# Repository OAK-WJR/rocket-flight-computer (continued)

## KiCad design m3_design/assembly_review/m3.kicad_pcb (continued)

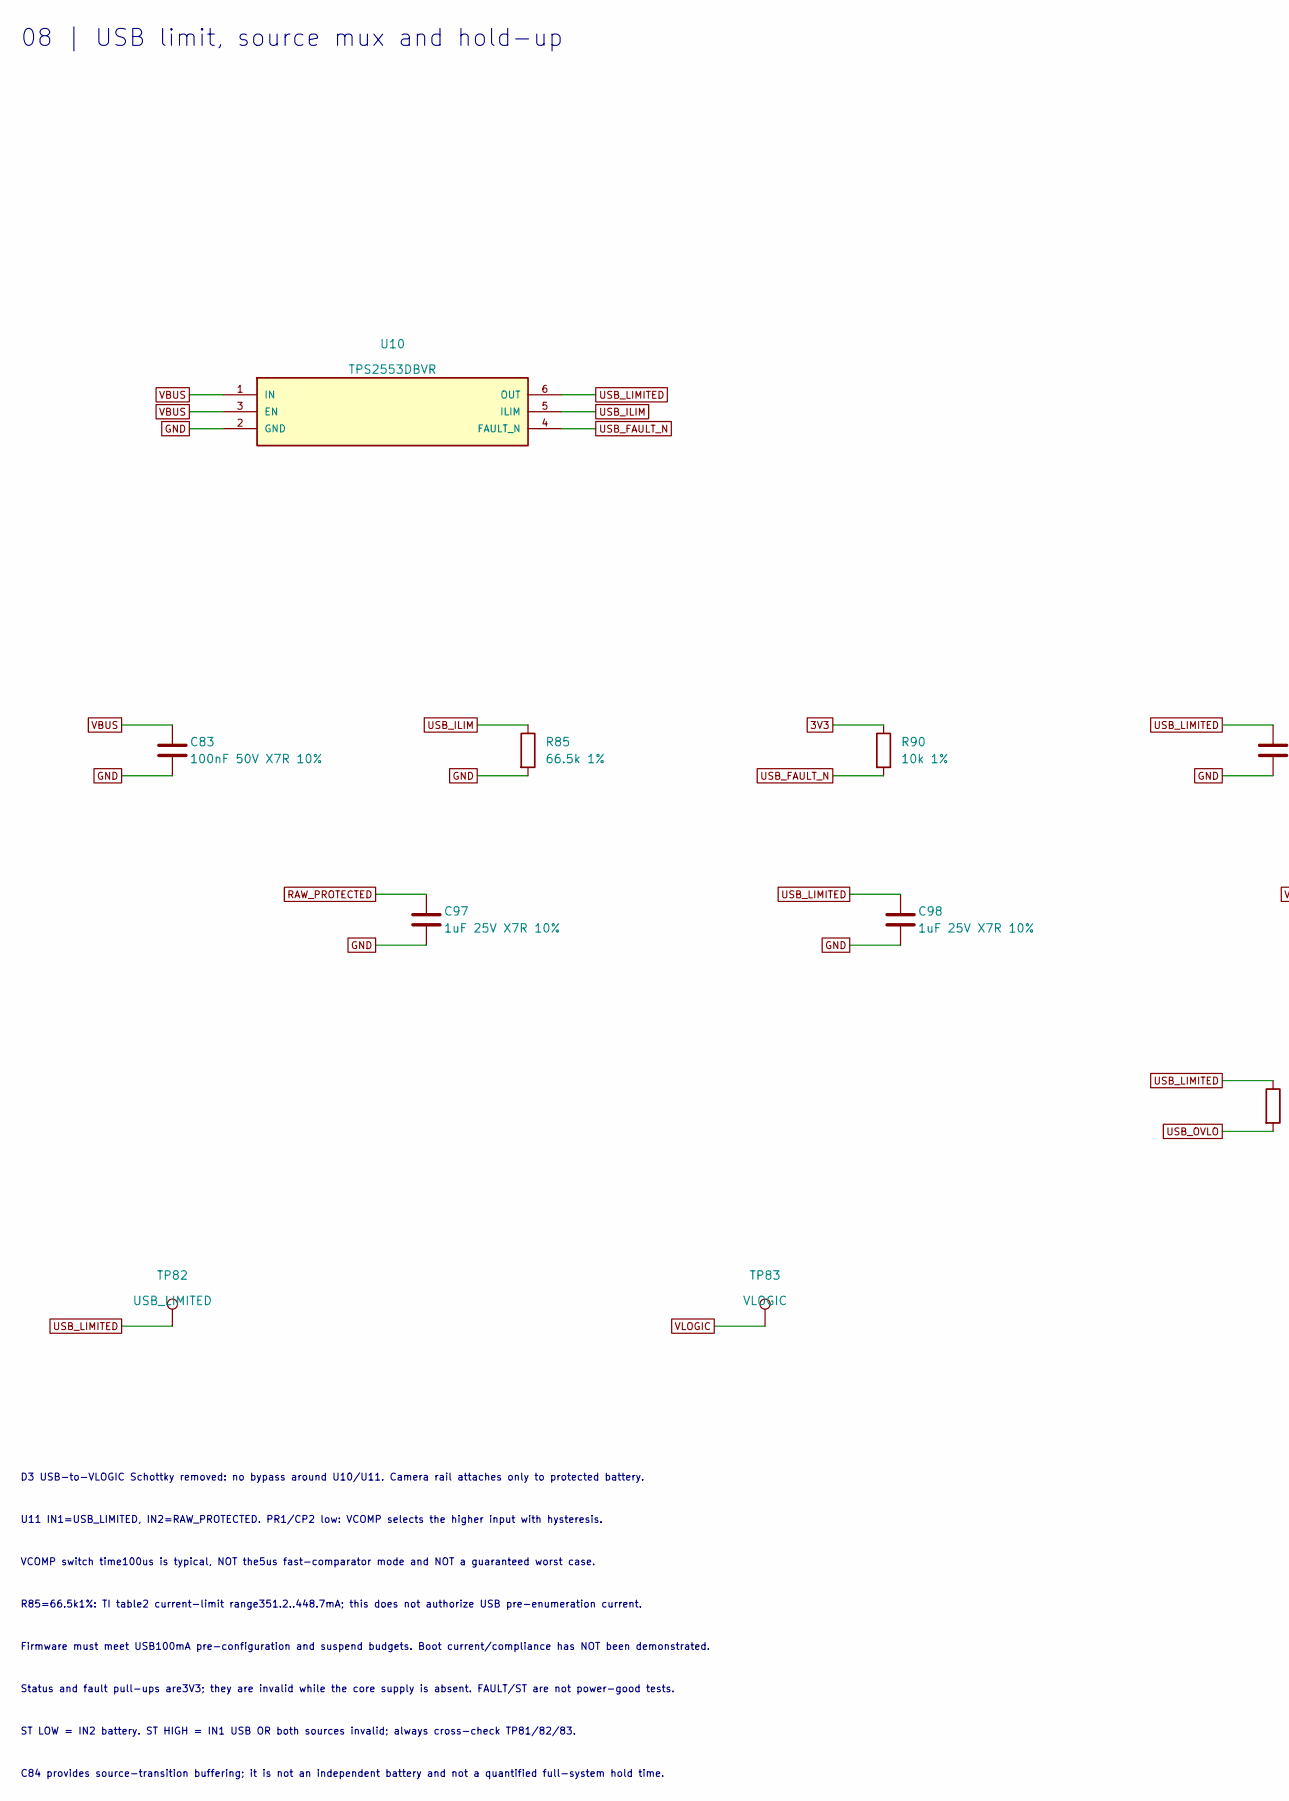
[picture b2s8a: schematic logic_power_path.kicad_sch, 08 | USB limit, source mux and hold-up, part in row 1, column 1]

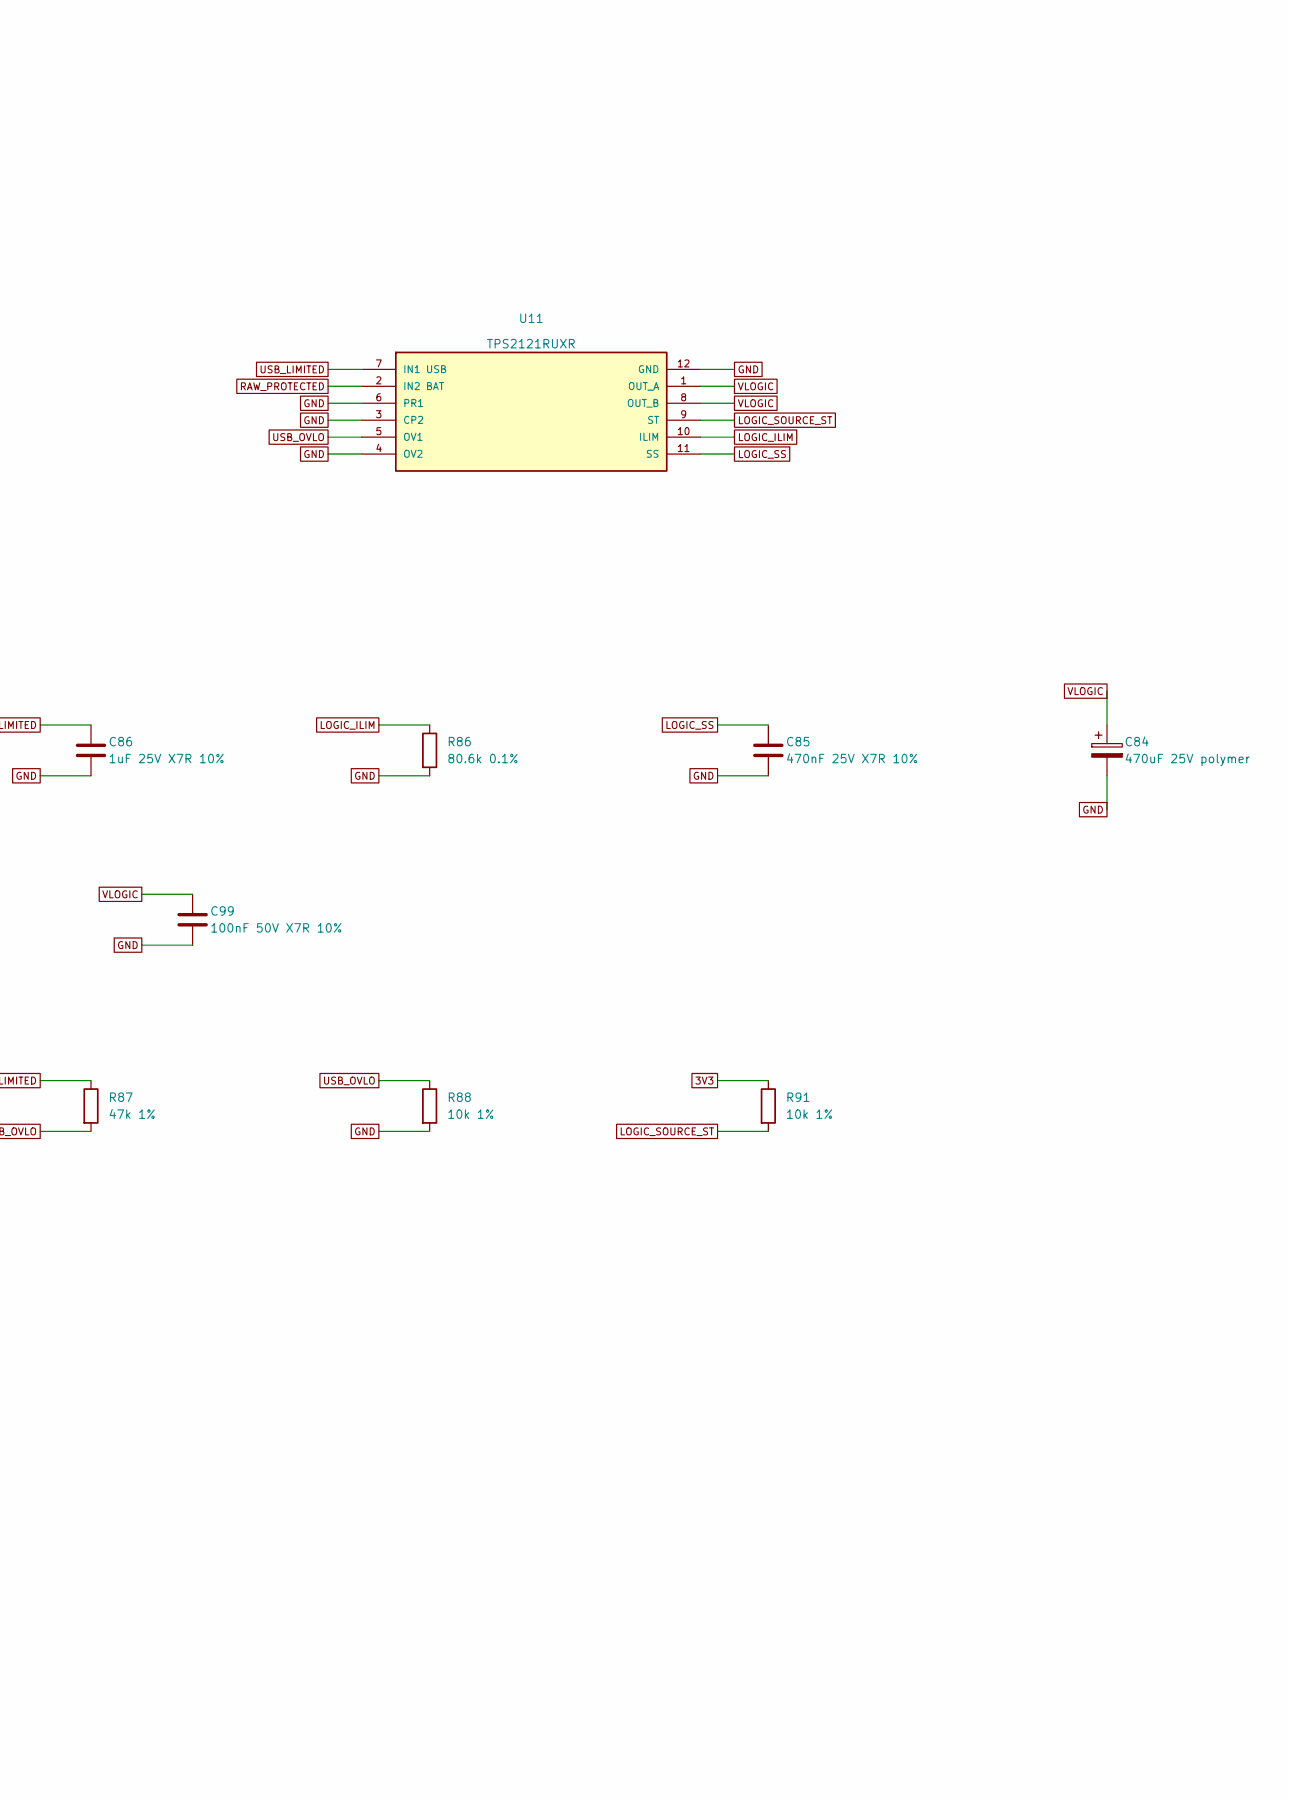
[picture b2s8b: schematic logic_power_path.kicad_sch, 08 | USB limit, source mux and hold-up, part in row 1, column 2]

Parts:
C83: 100nF 50V X7R 10%; C_0603_1608Metric; Manufacturer Part CC0603KRX7R9BB104; LCSC C14663
C84: 470uF 25V polymer; M3_MA_8x10; Manufacturer Part MA25V470M8x10; LCSC C46550466
C85: 470nF 25V X7R 10%; C_0603_1608Metric; Manufacturer Part CL10B474KA8NNNC; LCSC C1623
C86, C97, C98: 1uF 25V X7R 10%; C_0603_1608Metric; Manufacturer Part CL10B105KA8NNNC; LCSC C29936
C99: 100nF 50V X7R 10%; C0402; Manufacturer Part CL05B104KB54PNC; LCSC C307331
R85: 66.5k 1%; R_0603_1608Metric; Manufacturer Part RC0603FR-0766K5L; LCSC C137691
R86: 80.6k 0.1%; R_0603_1608Metric; Manufacturer Part RT0603BRD0780K6L; LCSC C861568
R87: 47k 1%; R_0603_1608Metric; Manufacturer Part 0603WAF4702T5E; LCSC C25819
R88, R90, R91: 10k 1%; R_0603_1608Metric; Manufacturer Part 0603WAF1002T5E; LCSC C25804
TP82: USB_LIMITED; M3_TestPad_1.5
TP83: VLOGIC; M3_TestPad_1.5
U10: TPS2553DBVR; M3_TPS2553_DBV; Manufacturer Part TPS2553DBVR; LCSC C55266
U11: TPS2121RUXR; M3_TPS2121_RUX; Manufacturer Part TPS2121RUXR; LCSC C485916

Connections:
3V3: R90.1, R91.1; also elsewhere on the board
GND: C83.2, C84.2, C85.2, C86.2, C97.2, C98.2, C99.2, R85.2, R86.2, R88.2, U10.2 (GND), U11.3 (CP2), U11.4 (OV2), U11.6 (PR1), U11.12 (GND); also elsewhere on the board
LOGIC_ILIM: R86.1, U11.10 (ILIM)
LOGIC_SOURCE_ST: R91.2, U11.9 (ST); also elsewhere on the board
LOGIC_SS: C85.1, U11.11 (SS)
RAW_PROTECTED: C97.1, U11.2 (IN2 BAT); also elsewhere on the board
USB_FAULT_N: R90.2, U10.4 (FAULT_N); also elsewhere on the board
USB_ILIM: R85.1, U10.5 (ILIM)
USB_LIMITED: C86.1, C98.1, R87.1, TP82.1, U10.6 (OUT), U11.7 (IN1 USB)
USB_OVLO: R87.2, R88.1, U11.5 (OV1)
VBUS: C83.1, U10.1 (IN), U10.3 (EN); also elsewhere on the board
VLOGIC: C84.1, C99.1, TP83.1, U11.1 (OUT_A), U11.8 (OUT_B); also elsewhere on the board

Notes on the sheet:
08 | USB limit, source mux and hold-up
D3 USB-to-VLOGIC Schottky removed: no bypass around U10/U11. Camera rail attaches only to protected battery.
U11 IN1=USB_LIMITED, IN2=RAW_PROTECTED. PR1/CP2 low: VCOMP selects the higher input with hysteresis.
VCOMP switch time100us is typical, NOT the5us fast-comparator mode and NOT a guaranteed worst case.
R85=66.5k1%: TI table2 current-limit range351.2..448.7mA; this does not authorize USB pre-enumeration current.
Firmware must meet USB100mA pre-configuration and suspend budgets. Boot current/compliance has NOT been demonstrated.
Status and fault pull-ups are3V3; they are invalid while the core supply is absent. FAULT/ST are not power-good tests.
ST LOW = IN2 battery. ST HIGH = IN1 USB OR both sources invalid; always cross-check TP81/82/83.
C84 provides source-transition buffering; it is not an independent battery and not a quantified full-system hold time.

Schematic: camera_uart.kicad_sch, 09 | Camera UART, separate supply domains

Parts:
C90, C93: 100nF 50V X7R 10%; C_0603_1608Metric; Manufacturer Part CC0603KRX7R9BB104; LCSC C14663
C91: 1uF 50V X7R 10%; C_1206_3216Metric; Manufacturer Part CL31B105KBHNNNE; LCSC C1848
C92: 4.7uF 16V X5R 10%; C0603; Manufacturer Part CL10A475KO8NNNC; LCSC C19666
C100: 100nF 50V X7R 10%; C0402; Manufacturer Part CL05B104KB54PNC; LCSC C307331
D400, D401: ESD103-B1-02EL; M3_TSLP_2_20; Manufacturer Part ESD103-B1-02EL E6327; LCSC C535146
R100, R101, R103: 1k 1%; R_0603_1608Metric; Manufacturer Part 0603WAF1001T5E; LCSC C21190
R102: 10k 1%; R_0603_1608Metric; Manufacturer Part 0603WAF1002T5E; LCSC C25804
U12: TXU0202DCUR; M3_TXU0202_DCU; Manufacturer Part TXU0202DCUR; LCSC C5186957
U13: TPS70933DBVR; M3_TPS709_DBV; Manufacturer Part TPS70933DBVR; LCSC C89347

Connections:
3V3: C90.1, C100.1, U12.3 (VCCA MCU); also elsewhere on the board
CAM_5V: C91.1, U13.1 (IN); also elsewhere on the board
CAM_IO_3V3: C92.1, C93.1, R103.1, U12.7 (VCCB CAMERA), U13.5 (OUT3.3V)
CAM_MCU_RX: U12.4 (A2Y RX OUTPUT); also elsewhere on the board
CAM_MCU_TX: U12.5 (A1 TX INPUT); also elsewhere on the board
CAM_RX_BUFFER: R100.2, U12.1 (B2 FROM CAMERA)
CAM_RX_WIRE: D401.1 (A1), R100.1; also elsewhere on the board
CAM_TX_BUFFER: R101.1, U12.8 (B1Y TO CAMERA)
CAM_TX_WIRE: D400.1 (A1), R101.2; also elsewhere on the board
CAM_UART_OE: R102.1, U12.6 (OE); also elsewhere on the board
GND: C90.2, C91.2, C92.2, C93.2, C100.2, D400.2 (A2), D401.2 (A2), R102.2, R103.2, U12.2 (GND), U13.2 (GND); also elsewhere on the board

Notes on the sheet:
09 | Camera UART, separate supply domains
U12 A-port=MCU3V3. B-port=U13 camera-derived3V3. Never substitute CAM5V for VCCB.
Reset: R102 holds OE LOW. Set TX idle HIGH before OE; disable OE before power-down.
U13 EN is internally biased: leave pin3 OPEN, not tied to IN. Pin4 is NC.
UART is 3.3V, not RS232. TXU input operating range0..5.5V is not a cable battery-short rating.
Camera VIH/VIL/VOH/VOL and timing remain unmeasured. Verify at TP75/76/90 before qualification.
Existing v0.2 bench firmware keeps camera OFF and does not operate this UART. Full system incomplete.
R8: PE8/pin38 UART7_TX and PE7/pin37 UART7_RX use AF7, no flow control (never AF7 on PE9 or PE10); off the ROM loader's USART3. R10: PE9/pin39 CAM_UART_OE drives OE as a GPIO; R102 10k holds it low (R19-MCU-03).

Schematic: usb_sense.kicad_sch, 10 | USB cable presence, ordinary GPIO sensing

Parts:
R9: 1k; R0402; Manufacturer Part 0402WGF1001TCE; LCSC C11702
R110: 1k 1%; R_0603_1608Metric; Manufacturer Part 0603WAF1001T5E; LCSC C21190

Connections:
GND: R110.2; also elsewhere on the board
VBUS: R9.1; also elsewhere on the board
VBUS_SENSE: R9.2, R110.1; also elsewhere on the board

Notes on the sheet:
10 | USB cable presence, ordinary GPIO sensing
PC8 / U1 pin65 (R8) is a regular FT_h GPIO input (EXTI8). PA9 remains NC. D+/D- are unchanged.
R9 = R110 = 1k (R4): PC8 <= 1.01 V when D4 back-feeds VBUS with the D+ pull-up on, 2.18 V at VBUS 4.40 V. Probe R9.2 / R110.1; TP92 removed (AUD-5). No internal pull-up/down.
Input range and tolerance calculation uses DS12110 Rev11, Tables14/112 and50/147.
Use software attach/detach from PC8. Do NOT enable native PA9 VBUS sensing (VBDEN).
USB 48MHz source, descriptors, suspend current and actual enumeration remain unqualified.
VBUS decay depends on C28/C83/C86 and mux/switch leakage. RC estimates are conditional.
Measure reset/unpowered input, USB plug/unplug, discharge and hot leakage before acceptance.
Old v0.2-v0.5 firmware is bound to previous board hashes, not to this new candidate.

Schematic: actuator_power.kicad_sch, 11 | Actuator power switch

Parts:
C120: 1uF 25V X7R 10%; C_0603_1608Metric; Manufacturer Part CL10B105KA8NNNC; LCSC C29936
Q120, Q121: AONR21357; M3_AONR21357_DFN3x3A_EP1; Manufacturer Part AONR21357; LCSC C431196
Q122: AO3400A; SOT-23-3_L2.9-W1.3-P1.90-LS2.4-BR; Manufacturer Part AO3400A; LCSC C20917
R119, R120: 100k; R0402; Manufacturer Part 0402WGF1003TCE; LCSC C25741
R121: 10k; R0402; Manufacturer Part 0402WGF1002TCE; LCSC C25744
R122: 1k; R0402; Manufacturer Part 0402WGF1001TCE; LCSC C11702
R123: 2k; R0402; Manufacturer Part 0402WGF2001TCE; LCSC C4109
TP120: RAW_ACT; M3_TestPad_1.5
TP121: ACT_GATE; M3_TestPad_1.5

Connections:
ACT_DRV: Q122.3 (D), R121.2
ACT_EN: Q122.1 (G), R122.2, R123.1; also elsewhere on the board
ACT_EN_MCU: R122.1; also elsewhere on the board
ACT_FET_S: C120.1, Q120.1 (S), Q120.2 (S), Q120.3 (S), Q121.1 (S), Q121.2 (S), Q121.3 (S), R119.2, R120.1
ACT_GATE: C120.2, Q120.4 (G), Q121.4 (G), R119.1, R120.2, R121.1, TP121.1
BAT_IN: Q120.5 (D), Q120.6 (D), Q120.7 (D), Q120.8 (D), Q120.9 (D); also elsewhere on the board
GND: Q122.2 (S), R123.2; also elsewhere on the board
RAW_ACT: Q121.5 (D), Q121.6 (D), Q121.7 (D), Q121.8 (D), Q121.9 (D), TP120.1; also elsewhere on the board

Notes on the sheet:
R10 single screw switch (owner 2026-10-28): J400 powers and arms the board; J124 is removed. Q120/Q121 remain the pyro-bus load switch feeding RAW_ACT.
PC1 (U1.16) drives ACT_EN_MCU through R122 1k to Q122; R123 2k holds Q122 off in reset, unpowered or against a 30k internal pull-up (gate <=0.22V at 3.6V; R18-MCU-01). PC1 high gives about 2.2V gate. Q124 uses a separate MCU fire pin and its retained gate network.
D-SS-04: hold PC1 and PE4 low for passive cold screening; after prior enable wait >=1 s and verify RAW_ACT discharged / ACT_GATE off. Qualify passive fault bands and refuse ground faults BEFORE PC1 enable; then PC1 high, PE4 low >=100 ms before powered-bus checks.
AUD-3: Q120/Q121 AONR21357, C120 1uF 25V X7R. Hot resistance and turn-on SOA remain bench qualifications.
R18-SAF-02: R120 100k at Q120 and R119 100k at Q121 each tie a P-FET gate to ACT_FET_S through via-free local bottom copper, so one open via or track leaves both FETs off. ACT_GATE/BAT_ENABLE barrels keep 1mm inner clearance.
C121 removed; servos use external pack power and return. RAW_ACT feeds R134 and the sole ARM1_SENSE bus divider; no feed directly from BAT_IN or RAW_PROTECTED.
R134 limits a shorted igniter; normal physical fire current <=20 ms. Firmware timing and pulse qualification: sources/r10_design/parts_qualification.md; no firmware implemented.

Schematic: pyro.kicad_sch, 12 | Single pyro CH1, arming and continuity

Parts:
C126: 220nF 25V X7R; C0603; Manufacturer Part CL10B224KA8NNNC; LCSC C21120
C127, C129: 10nF 50V X7R 10%; C0603; Manufacturer Part 0603B103K500NT; LCSC C57112
C128: 100nF 50V X7R 10%; C_0603_1608Metric; Manufacturer Part GCJ188R71H104KA12D; LCSC C161115
D120: BAT54A; SOT-23-3_L2.9-W1.3-P1.90-LS2.4-BR; Manufacturer Part BAT54A; LCSC C8591
J121: DB125-3.5-2P-BK-S; M3_DB125_2P_BK; Manufacturer Part DB125-3.5-2P-BK-S; LCSC C52993880
Q124: AON7524; M3_AON7524_DFN3x3A; Manufacturer Part AON7524; LCSC C431195
R126: 220R; R0805; Manufacturer Part 0805W8F2200T5E; LCSC C17557
R127: 1k; R0402; Manufacturer Part 0402WGF1001TCE; LCSC C11702
R128, R131: 10k; R0402; Manufacturer Part 0402WGF1002TCE; LCSC C25744
R129, R132, R173, R175: 5.1k; R0402; Manufacturer Part 0402WGF5101TCE; LCSC C25905
R130, R133, R178, R180: 2k; R0402; Manufacturer Part 0402WGF2001TCE; LCSC C4109
R134: 2R 1% 2W pulse; R2512; Manufacturer Part CRM2512-FX-2R00ELF; LCSC C3013496
TP122: PYRO1_GATE; M3_TestPad_1.5

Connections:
3V3: D120.3 (A); also elsewhere on the board
ARM1_SENSE: C129.1, R133.1, R175.2, R180.1; also elsewhere on the board
ARM1_SENSE_MID: R132.2, R175.1
GND: C126.2, C127.2, C128.2, C129.2, Q124.1 (S), Q124.2 (S), Q124.3 (S), R127.2, R128.2, R130.2, R133.2, R178.2, R180.2; also elsewhere on the board
PYRO1_COLD: D120.1 (K1), R131.2
PYRO1_CONT: C127.1, R129.2, R130.1, R178.1; also elsewhere on the board
PYRO1_CONT_MID: R129.1, R173.2
PYRO1_GATE: C126.1, Q124.4 (G), R126.2, R128.1, TP122.1
PYRO1_GATE_N: R126.1, R127.1; also elsewhere on the board
PYRO1_IGN: J121.2, R134.1
PYRO1_OUT: C128.1, J121.1, Q124.5 (D), R131.1, R173.1
RAW_ACT: R132.1, R134.2; also elsewhere on the board

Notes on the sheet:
R10 single screw switch: RAW_ACT directly feeds R134.2 and R132.1 behind Q120/Q121; no separate ARM terminal or PYRO1_BUS net. J121.2 IGN, J121.1 OUT.
Power switch on last, off first; the pyro channel is live whenever the board is on. No firing before accelerometer and barometer launch detection; bench USB or e-match disconnected.
R10 uses default board clearance; accepted loss of R9 single-defect spacing margins does not waive functional reset, gate or divider safety.
Ground bus/continuity checks refuse firing; in flight readings only log/annunciate and never veto a fire. Refresh 960-cycle IWDG immediately before PE4 rises; never refresh while fire is active. Normal physical current <=20 ms; fault physical current <=36 ms; complete SAFETY and refresh <=5 ms afte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
AVA follow-up: ARM1_SENSE onPC5 is the sole RAW_ACT bus reading. R177/R124/R125/R182/R172/C122 and RAW_ACT_SENSE are removed; PB0 is NC/analog. Continuity divider and both split-divider fault ratios stay. Audit2 removes R168/R170 and _MCU tails: filtered PYRO1_CONT and ARM1_SENSE directly feedPC0/P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

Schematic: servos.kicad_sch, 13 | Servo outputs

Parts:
D121: SRV05-4; SOT-23-6_L2.9-W1.6-P0.95-LS2.8-BL; Manufacturer Part SRV05-4.TCT; LCSC C13612
J122: DB125-3.5-5P-GN-S; M3_DB125_5P_GN; Manufacturer Part DB125-3.5-5P-GN-S; LCSC C3646874
R150, R151, R152, R153: 1k 0603; R_0603_1608Metric; Manufacturer Part 0603WAF1001T5E; LCSC C21190
R154, R155, R156, R157: 10k; R0402; Manufacturer Part 0402WGF1002TCE; LCSC C25744

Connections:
3V3: D121.5 (VCC); also elsewhere on the board
GND: D121.2 (GND), J122.5 (GND), R154.2, R155.2, R156.2, R157.2; also elsewhere on the board
SERVO1_MCU: D121.1 (IO1), R150.1, R154.1; also elsewhere on the board
SERVO1_OUT: J122.1 (SERVO1), R150.2
SERVO2_MCU: D121.3 (IO2), R151.1, R155.1; also elsewhere on the board
SERVO2_OUT: J122.2 (SERVO2), R151.2
SERVO3_MCU: D121.4 (IO3), R152.1, R156.1; also elsewhere on the board
SERVO3_OUT: J122.3 (SERVO3), R152.2
SERVO4_MCU: D121.6 (IO4), R153.1, R157.1; also elsewhere on the board
SERVO4_OUT: J122.4 (SERVO4), R153.2

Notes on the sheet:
R10 owner screw terminals: J122 pins1/2/3/4 SERVO1/2/3/4_OUT, pin5 GND signal reference. No servo positive connection on board.
Each servo power AND motor return run directly to the pack in the harness. Board GND is signal reference; residual shared return must satisfy the harness calculation.
Keep four1k series resistors,10k pull-downs andSRV05-4 clamp. Board cannot cut servo power. Command neutral<=50ms after reset; bench servo/harness failsafe.
J122 DORABO DB1253.5mm5posgreenC3646874; bodycount andfullpinlegends distinguish from greenbattery. Clamp leads28-16AWG; qualifiedferrules/splices forthinnerleads; no solder-tinned strandedwire. Removeobsolete servo-plug tieholes.

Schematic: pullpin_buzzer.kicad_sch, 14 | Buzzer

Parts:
D123: 1N5819WS; SOD-323_L1.8-W1.3-LS2.5-RD; Manufacturer Part 1N5819WS; LCSC C191023
LS120: MLT-5020; M3_MLT5020_3pad; Manufacturer Part MLT-5020; LCSC C94598
Q123: AO3400A; SOT-23-3_L2.9-W1.3-P1.90-LS2.4-BR; Manufacturer Part AO3400A; LCSC C20917
R162: 1k 0805; R0805; Manufacturer Part 0805W8F1001T5E; LCSC C17513
R163: 10k; R0402; Manufacturer Part 0402WGF1002TCE; LCSC C25744

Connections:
3V3: D123.1 (K), LS120.1 (+); also elsewhere on the board
BUZZ_DRV: R162.1; also elsewhere on the board
BUZZ_G: Q123.1 (G), R162.2, R163.1
BUZZ_OUT: D123.2 (A), LS120.2 (-), Q123.3 (D)
GND: Q123.2 (S), R163.2; also elsewhere on the board

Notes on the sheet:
14 | Buzzer; AUD-4 removes J123, R160/R161, C160 and D122. PC13 U1.7 is NC/analog, with no pull-pin or EXTI13.
LS120 MLT-5020: pad1 positive, pad2 negative, pad3 isolated mechanical tab. Huaneng 2021-05-27 drawing; body5.0 +/-0.3 mm, height2.0 +/-0.2 mm.
BUZZ_DRV = PC14 U1.8 (R10); R162 1k and R163 10k retain the gate network. Use4kHz,50% duty GPIO software toggle; backup-domain GPIO <=2MHz. Never drive the coil with DC.
Keep LSEON=0 and do not assign RTC/clock outputs to PC14; VBAT=3V3, so backup-domain settings survive NRST. Buzzer and servo neutral behavior remain bench qualifications.

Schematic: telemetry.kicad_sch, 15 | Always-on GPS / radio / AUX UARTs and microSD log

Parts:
C460: 100nF 50V X7R 10%; C_0603_1608Metric; Manufacturer Part CC0603KRX7R9BB104; LCSC C14663
C461: 22uF 25V X7R 10%; M3_GRM32_1210; Manufacturer Part GRM32ER71E226KE15L; LCSC C21397
D410, D411, D420, D421, D440, D441: ESD103-B1-02EL; M3_TSLP_2_20; Manufacturer Part ESD103-B1-02EL E6327; LCSC C535146
J410, J420, J440: DB125-3.5-4P-GN-S; M3_DB125_4P_GN; Manufacturer Part DB125-3.5-4P-GN-S; LCSC C2757925
J430: 472192001; M3_MICROSD_MOLEX_472192001; Manufacturer Part 472192001; LCSC C164170
R440, R441, R450, R451, R470, R471: 1k 1%; R_0603_1608Metric; Manufacturer Part 0603WAF1001T5E; LCSC C21190
R460, R461, R462, R463, R464: 10k 1%; R_0603_1608Metric; Manufacturer Part 0603WAF1002T5E; LCSC C25804

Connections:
3V3: C460.1, C461.1, J430.4 (VDD), R460.2, R461.2, R462.2, R463.2, R464.2; also elsewhere on the board
AUX_RX_WIRE: D441.1 (A1), J440.4 (RXI), R470.1
AUX_TX_WIRE: D440.1 (A1), J440.3 (TXO), R471.2
GND: C460.2, C461.2, D410.2 (A2), D411.2 (A2), D420.2 (A2), D421.2 (A2), D440.2 (A2), D441.2 (A2), J410.2 (GND), J420.2 (GND), J430.6 (VSS), J430.9 (G2), J430.10 (G3), J430.11 (G4), J430.12 (G1), J440.2 (GND); also elsewhere on the board
GPS_RX_MCU: R440.2; also elsewhere on the board
GPS_RX_WIRE: D411.1 (A1), J410.4 (RXI), R440.1
GPS_TX_MCU: R441.1; also elsewhere on the board
GPS_TX_WIRE: D410.1 (A1), J410.3 (TXO), R441.2
PORT_4V8: J410.1 (4V8), J420.1 (4V8), J440.1 (4V8); also elsewhere on the board
RADIO_RX_MCU: R450.2; also elsewhere on the board
RADIO_RX_WIRE: D421.1 (A1), J420.4 (RXI), R450.1
RADIO_TX_MCU: R451.1; also elsewhere on the board
RADIO_TX_WIRE: D420.1 (A1), J420.3 (TXO), R451.2
SD_CS: J430.2 (CD_DAT3_CS), R460.1; also elsewhere on the board
SD_DAT1: J430.8 (DAT1), R463.1
SD_DAT2: J430.1 (DAT2), R464.1
SD_MISO: J430.7 (DAT0_DO), R462.1; also elsewhere on the board
SD_MOSI: J430.3 (CMD_DI), R461.1; also elsewhere on the board
SD_SCK: J430.5 (CLK); also elsewhere on the board

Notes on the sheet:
R10: always-on GPS J410, radio J420 and spare AUX J440 (D-R19-14, owner 2026-10-30), three electrically identical ports. DB1254pos pins1 PORT_4V8,2 GND,3 board TX,4 board RX; harness crosses TX to endpoint RX.
Port UARTs: J410 USART3 PD8 TX / PD9 RX AF7; J420 UART5 PB13 TX / PB12 RX AF14; J440 USART6 PC6 TX / PC7 RX AF7 (ST DS12110 Rev 8 Table 11 p91 PB12/PB13, Table 12 p92 PC6/PC7, Table 13 p94 PD8/PD9). Firmware maps each device to a port; default GPS J410, radio J420, AUX spare. Direct MCU UART throug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
RX FT_h / FT_u: digital0..5V only, pulls disabled throughout use. Operating pull limit is relevant IO supply+0.3V (DS12110 Rev 8 Table 122 n3 p215 / Table 157 n7 p247), distinct from Table 119 absolute stress. Board off: no self-powered module;1k is not powered-off isolation.
J430 Molex472192001 is a locking hinged microSD socket, no eject spring or card-detect switch. SPI3 PC10/11/12 AF6, PD0 software CS with10k pull-up. QSPI remains the crash-safe primary log.
Card pins1 DAT2,2 CS,3 MOSI/CMD,4 3V3,5 SCK,6 GND,7 MISO/DAT0,8 DAT1; four shield tabs to GND. R460-R46410k pull-ups on CS/CMD/DAT0/DAT1/DAT2; C460100nF plus C46122uF at card supply; no SCK pull.
Power-up SD: CS high, MOSI high, >=74 clocks at100-400kHz; enter SPI with CMD0. Limit run clock<=25MHz, card write<=200mA and idle<=30mA as bench-qualified allocations. No blocking card operation in flight; card removal only with board off.
ROM loader drives PC11 SPI3_MISO while CS stays high throughR460; card must remain deselected. Disable synchronous trace because PC12 can be TRACED3. CS high before AF6 configuration.
Radio messages may never arm/fire. LR900-F band890-915MHz: use channels12-25(902-915MHz) or maker-confirmed FHSS set. Bench-qualify installed RF immunity.
J410/J420/J440 are unkeyedgreenDB1253.5mm4posC2757925. Labelpower/GND/TX/RXperpin; clamp28-16AWGqualifiedferrules/splices, verifypolarity andharnesscrossing beforepower. Thinnermoduleleadsmustnotbeclampeddirectly.

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
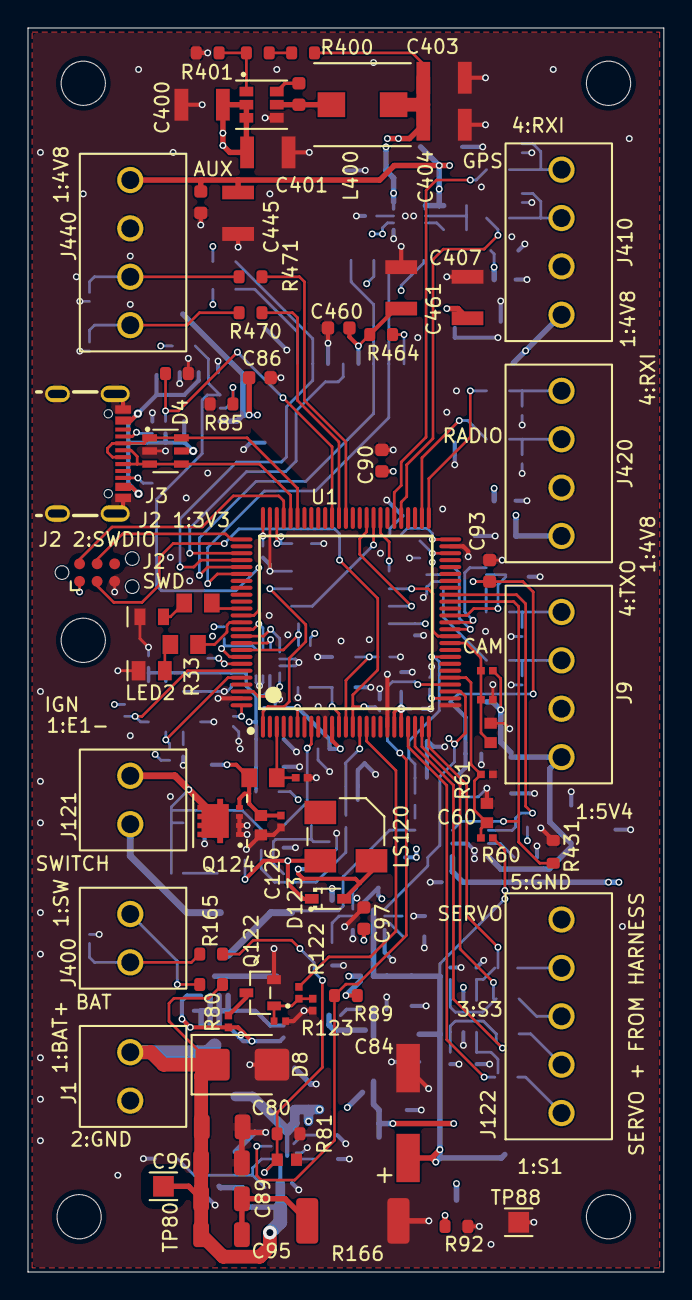
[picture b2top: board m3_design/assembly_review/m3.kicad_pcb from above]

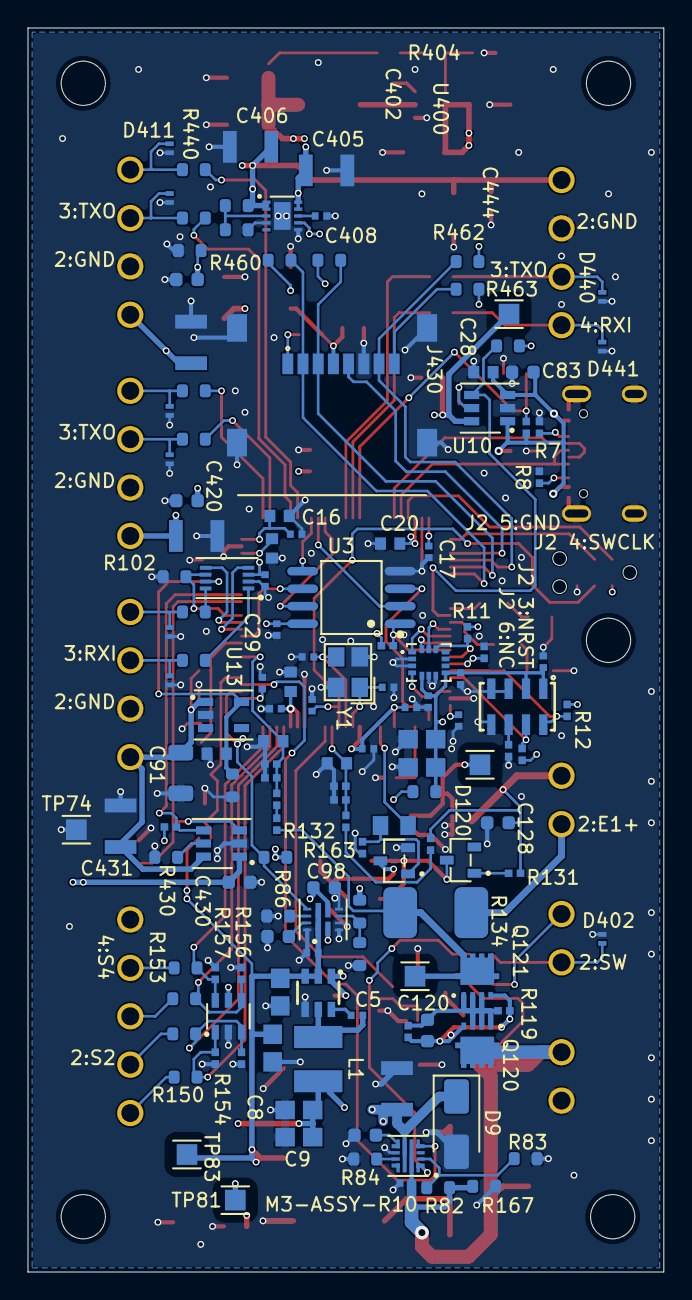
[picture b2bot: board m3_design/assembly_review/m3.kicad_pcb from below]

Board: 4 copper layers, 46.0 x 90.0 mm, 216 parts (142 on the bottom side), 121 nets.

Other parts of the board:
C123: 10nF 50V X7R 10%; C0402

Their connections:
ACT_EN: C123.1; also elsewhere on the board
GND: C123.2; also elsewhere on the board

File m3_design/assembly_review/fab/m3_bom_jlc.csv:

Comment,Designator,Footprint,LCSC Part #,Manufacturer Part,Qty,Assembly
100nF 50V X7R 10%,"C5,C13,C14,C15,C16,C17,C18,C21,C24,C29,C30,C31,C32,C88,C99,C100",C0402,C307331,CL05B104KB54PNC,16,SMT
22uF 25V X5R 20%,"C6,C7,C8,C9,C10,C11",C0805,C45783,CL21A226MAQNNNE,6,SMT
2.2uF 16V X5R 10%,"C19,C20",C0603,C23630,CL10A225KO8NNNC,2,SMT
1uF 50V X5R 10%,C22,C0603,C15849,CL10A105KB8NNNC,1,SMT
4.7uF 16V X5R 10%,"C23,C28,C92",C0603,C19666,CL10A475KO8NNNC,3,SMT
10pF 50V C0G 5%,"C25,C26",C0402,C32949,CL05C100JB5NNNC,2,SMT
10nF 50V X7R 10%,"C60,C94,C127,C129",C0603,C57112,0603B103K500NT,4,SMT
10uF 50V X5R 10%,"C80,C96",C_1206_3216Metric,C13585,CL31A106KBHNNNE,2,SMT
4.7nF 50V C0G 5%,C81,C_0603_1608Metric,C85980,GRM1885C1H472JA01D,1,SMT
22uF 25V X7R 10%,"C82,C400,C401,C403,C404,C405,C406,C407,C411,C421,C431,C445,C461",M3_GRM32_1210,C21397,GRM32ER71E226KE15L,13,SMT
100nF 50V X7R 10%,"C83,C90,C93,C402,C410,C420,C430,C444,C460",C_0603_1608Metric,C14663,CC0603KRX7R9BB104,9,SMT
470nF 25V X7R 10%,C85,C_0603_1608Metric,C1623,CL10B474KA8NNNC,1,SMT
1uF 25V X7R 10%,"C86,C97,C98,C120",C_0603_1608Metric,C29936,CL10B105KA8NNNC,4,SMT
220nF 25V X7R,"C87,C126",C0603,C21120,CL10B224KA8NNNC,2,SMT
22uF 25V X5R 10%,"C89,C95",C_1206_3216Metric,C12891,CL31A226KAHNNNE,2,SMT
1uF 50V X7R 10%,C91,C_1206_3216Metric,C1848,CL31B105KBHNNNE,1,SMT
10nF 50V X7R 10%,"C123,C408",C0402,C15195,CL05B103KB5NNNC,2,SMT
100nF 50V X7R 10%,C128,C_0603_1608Metric,C161115,GCJ188R71H104KA12D,1,SMT
USBLC6-2SC6,D4,SOT-23-6_L2.9-W1.6-P0.95-LS2.8-BL,C7519,USBLC6-2SC6,1,SMT
SMBJ12CA,D8,D_SMB,C83849,SMBJ12CA,1,SMT
B340A-13-F,D9,D_SMA,C85098,B340A-13-F,1,SMT
BAT54A,D120,SOT-23-3_L2.9-W1.3-P1.90-LS2.4-BR,C8591,BAT54A,1,SMT
SRV05-4,D121,SOT-23-6_L2.9-W1.6-P0.95-LS2.8-BL,C13612,SRV05-4.TCT,1,SMT
1N5819WS,D123,SOD-323_L1.8-W1.3-LS2.5-RD,C191023,1N5819WS,1,SMT
ESD103-B1-02EL,"D400,D401,D402,D410,D411,D420,D421,D440,D441",M3_TSLP_2_20,C535146,ESD103-B1-02EL E6327,9,SMT
DB125-3.5-2P-GN-S,"J1,J400",M3_DB125_2P_GN,C466970,DB125-3.5-2P-GN-S,2,THT (JLC THT assembly)
USB-C 2.0,J3,USB-C_SMD-TYPE-C-31-M-12_1,C165948,TYPE-C-31-M-12,1,SMT
DB125-3.5-4P-GN-S,"J9,J410,J420,J440",M3_DB125_4P_GN,C2757925,DB125-3.5-4P-GN-S,4,THT (JLC THT assembly)
DB125-3.5-2P-BK-S,J121,M3_DB125_2P_BK,C52993880,DB125-3.5-2P-BK-S,1,THT (JLC THT assembly)
DB125-3.5-5P-GN-S,J122,M3_DB125_5P_GN,C3646874,DB125-3.5-5P-GN-S,1,THT (JLC THT assembly)
472192001,J430,M3_MICROSD_MOLEX_472192001,C164170,472192001,1,SMT
4.7uH,L1,IND-SMD_L4.0-W4.0,C57269,SWPA4030S4R7MT,1,SMT
6.8uH,L400,M3_SRP5030TA,C1329837,SRP5030T-6R8M,1,SMT
RED,LED1,M3_NCD0805R1_K1,C84256,NCD0805R1,1,SMT
YEL,LED2,M3_KT0805Y_A1,C2296,KT-0805Y,1,SMT
MLT-5020,LS120,M3_MLT5020_3pad,C94598,MLT-5020,1,SMT
AONR21357,"Q120,Q121",M3_AONR21357_DFN3x3A_EP1,C431196,AONR21357,2,SMT
AO3400A,"Q122,Q123",SOT-23-3_L2.9-W1.3-P1.90-LS2.4-BR,C20917,AO3400A,2,SMT
AON7524,Q124,M3_AON7524_DFN3x3A,C431195,AON7524,1,SMT
10k; 10k 1%,"R5,R10,R11,R61,R64,R104,R121,R128,R131,R154,R155,R156,R157,R163,R432",R0402,C25744,0402WGF1002TCE,15,SMT
5.1k,"R7,R8,R129,R132,R173,R175",R0402,C25905,0402WGF5101TCE,6,SMT
1k,"R9,R105,R122,R127",R0402,C11702,0402WGF1001TCE,4,SMT
4.7k,"R12,R13",R0402,C25900,0402WGF4701TCE,2,SMT
220R,"R32,R33,R126",R0805,C17557,0805W8F2200T5E,3,SMT
100k,"R60,R119,R120",R0402,C25741,0402WGF1003TCE,3,SMT
470k 1%,"R80,R165",R_0603_1608Metric,C23178,0603WAF4703T5E,2,SMT
300k 1%,R81,R_0603_1608Metric,C23024,0603WAF3003T5E,1,SMT
2M 0.1%,R82,R_0603_1608Metric,C4241878,MCT0603MD2004BP500,1,SMT
280k 0.1%,R83,R_0603_1608Metric,C705755,RT0603BRD07280KL,1,SMT
750R 0.1%,R84,R_0603_1608Metric,C861551,RT0603BRD07750RL,1,SMT
66.5k 1%,R85,R_0603_1608Metric,C137691,RC0603FR-0766K5L,1,SMT
80.6k 0.1%,R86,R_0603_1608Metric,C861568,RT0603BRD0780K6L,1,SMT
47k 1%,R87,R_0603_1608Metric,C25819,0603WAF4702T5E,1,SMT
10k 1%,"R88,R89,R90,R91,R102,R167,R460,R461,R462,R463,R464",R_0603_1608Metric,C25804,0603WAF1002T5E,11,SMT
3.3k 1%,R92,R_0603_1608Metric,C22978,0603WAF3301T5E,1,SMT
1k 1%; 1k 0603,"R100,R101,R103,R110,R150,R151,R152,R153,R440,R441,R450,R451,R470,R471",R_0603_1608Metric,C21190,0603WAF1001T5E,14,SMT
2k,"R123,R130,R133,R178,R180",R0402,C4109,0402WGF2001TCE,5,SMT
2R 1% 2W pulse,R134,R2512,C3013496,CRM2512-FX-2R00ELF,1,SMT
1k 0805,R162,R0805,C17513,0805W8F1001T5E,1,SMT
2.2R 1%,R164,R_0603_1608Metric,C22939,0603WAF220KT5E,1,SMT
0.36R 1% 2512,R166,M3_R2512_UR,C168925,25121WF360LT4E,1,SMT
56.2k 0.1%,R400,R_0603_1608Metric,C705784,RT0603BRD0756K2L,1,SMT
10k 0.1%,"R401,R403",R_0603_1608Metric,C95204,RT0603BRD0710KL,2,SMT
49.9k 0.1%,R402,R_0603_1608Metric,C705780,RT0603BRD0749K9L,1,SMT
2k 1%,R404,R_0603_1608Metric,C22975,0603WAF2001T5E,1,SMT
820R 1%,R405,R_0603_1608Metric,C23253,0603WAF8200T5E,1,SMT
22.6k 1%,R430,R_0603_1608Metric,C2999509,FRC0603F2262TS,1,SMT
100k 1%,R431,R_0603_1608Metric,C14675,RC0603FR-07100KL,1,SMT
STM32H743VIT6,U1,LQFP-100_L14.0-W14.0-P0.50-LS16.0-BL,C5271084,STM32H743VIT6TR,1,SMT
AP63203WU-7,U2,TSOT-26_L2.9-W1.6-P0.95-LS2.8-BL,C780769,AP63203WU-7,1,SMT
W25Q128JVSIQ,U3,SOIC-8_L5.3-W5.3-P1.27-LS8.0-BL,C97521,W25Q128JVSIQ,1,SMT
ISM6HG256X,U4,LGA-14_L3.0-W2.5-P0.50-TL,C51931514,ISM6HG256XTR,1,SMT
MS561101BA03,U5,SENSORS-SMD_MS5611-01BA03,C15639,MS561101BA03-50,1,SMT
TPS259470LRPWR,U9,M3_TPS25947_RPW,C3662793,TPS259470LRPWR,1,SMT
TPS2553DBVR,"U10,U402",M3_TPS2553_DBV,C55266,TPS2553DBVR,2,SMT
TPS2121RUXR,U11,M3_TPS2121_RUX,C485916,TPS2121RUXR,1,SMT
TXU0202DCUR,U12,M3_TXU0202_DCU,C5186957,TXU0202DCUR,1,SMT
TPS70933DBVR,U13,M3_TPS709_DBV,C89347,TPS70933DBVR,1,SMT
AP63201WU-7,U400,M3_AP63200_TSOT26,C2071044,AP63201WU-7,1,SMT
TPS7A9101DSKR,U401,M3_TPS7A91_DSK10,C2878140,TPS7A9101DSKR,1,SMT
25MHz CL8pF,Y1,CRYSTAL-SMD_4P-L3.2-W2.5-BL,C1985619,NX3225GA-25.000M-STD-CRG-2,1,SMT

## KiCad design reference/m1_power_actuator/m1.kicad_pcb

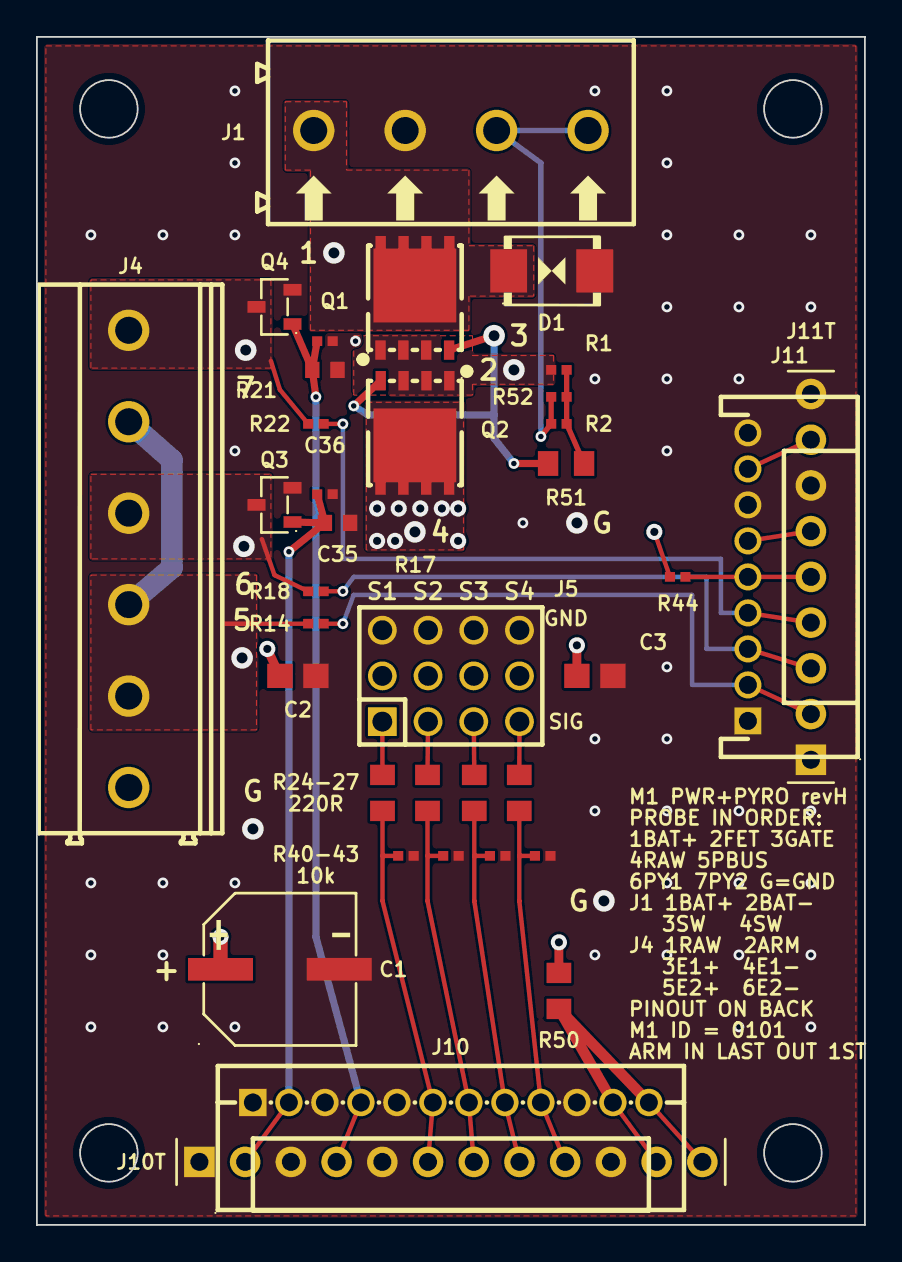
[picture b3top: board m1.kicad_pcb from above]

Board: 4 copper layers, 46.0 x 66.0 mm, 36 parts (0 on the bottom side), 27 nets.

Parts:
C1: 470uF/25V; CAP-SMD_BD8.0-L8.3-W8.3-LS9.0-FD_H10.5
C2, C3: 22uF; C0805
C35, C36: 10nF; C0603
D1: SMBJ12CA; SMB_L4.6-W3.6-LS5.3-BI
J1: BAT+/BAT-/SW/SW; CONN-TH_4P-P5.08_DIBO_DB128V-5.08
J4: ARM/PYRO; CONN-TH_6P-P5.08_DIBO_DB128V-5.08
J5: SERVO 3x4; HDR-TH_12P-P2.54-V-M-R3-C4-S2.54
J10: J-IF1 power+drive; CONN-TH_12P-P2.00_S12B-PH-K-S-LF-SN
J10T: J-IF1 solder/test row; HDR-TH_12P-P2.54-V-M-1x12
J11: J-IF2 sense+ID; CONN-TH_9P-P2.00_S9B-PH-K-S-LF-SN
J11T: J-IF2 solder/test row; HDR-TH_9P-P2.54-V-M-1x9
Q1, Q2: AON6403; PDFN-8_L5.6-W5.2-P1.27-LS6.1-BL
Q3, Q4: AO3400A; SOT-23-3_L2.9-W1.3-P1.90-LS2.4-BR
R1, R44: 100k; R0402
R2, R14, R18, R22, R40, R41, R42, R43: 10k; R0402
R17, R21: 1k; R0402
R24, R25, R26, R27: 220R; R0805
R50, R51: 0R; R0805
R52: DNP; R0402

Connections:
ARM_SENSE: J11.2, J11T.2, R14.2
BAT+: D1.1, J1.1, Q1.5, Q1.6, Q1.7, Q1.8, Q1.9
FET_S: Q1.1, Q1.2, Q1.3, Q2.1, Q2.2, Q2.3, R1.2
GATE_DRV: R1.1, R2.1, R51.1, R52.1
GATE_SW: Q1.4, Q2.4, R51.2
GND: C1.2, C2.2, C3.2, C35.2, C36.2, D1.2, J1.2, J5.3, J5.6, J5.9, J5.12, J10.1, J10.3, J10.5, J10.10, J10T.1, J10T.3, J10T.5, J10T.10, J11.1, J11.7, J11.9, J11T.1, J11T.7, J11T.9, Q3.2, Q4.2, R17.2, R21.2, R40.2, R41.2, R42.2, R43.2
ID0: J11.6, J11T.6
ID2: J11.8, J11T.8
PYRO1_CONT: J11.3, J11T.3, R18.2
PYRO1_GATE: C35.1, J10.2, J10T.2, Q3.1, R17.1
PYRO1_OUT: J4.4, Q3.3, R18.1
PYRO2_CONT: J11.4, J11T.4, R22.2
PYRO2_GATE: C36.1, J10.4, J10T.4, Q4.1, R21.1
PYRO2_OUT: J4.6, Q4.3, R22.1
PYRO_BUS: J4.2, J4.3, J4.5, R14.1
RAW: C1.1, C2.1, C3.1, J4.1, J5.2, J5.5, J5.8, J5.11, Q2.5, Q2.6, Q2.7, Q2.8, Q2.9, R44.1, R50.1
RAW_IF: J10.11, J10.12, J10T.11, J10T.12, R50.2
RAW_SENSE_PWR: J11.5, J11T.5, R44.2
SERVO1_MCU: J10.6, J10T.6, R24.1, R40.1
SERVO1_OUT: J5.1, R24.2
SERVO2_MCU: J10.7, J10T.7, R25.1, R41.1
SERVO2_OUT: J5.4, R25.2
SERVO3_MCU: J10.8, J10T.8, R26.1, R42.1
SERVO3_OUT: J5.7, R26.2
SERVO4_MCU: J10.9, J10T.9, R27.1, R43.1
SERVO4_OUT: J5.10, R27.2
SW_TERM: J1.3, J1.4, R2.2, R52.2
